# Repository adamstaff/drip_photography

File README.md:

# drip_photography
Board and code for a drip-photography timer

Based on 
https://petapixel.com/2016/06/04/build-diy-double-water-drip-system-high-speed-photos/

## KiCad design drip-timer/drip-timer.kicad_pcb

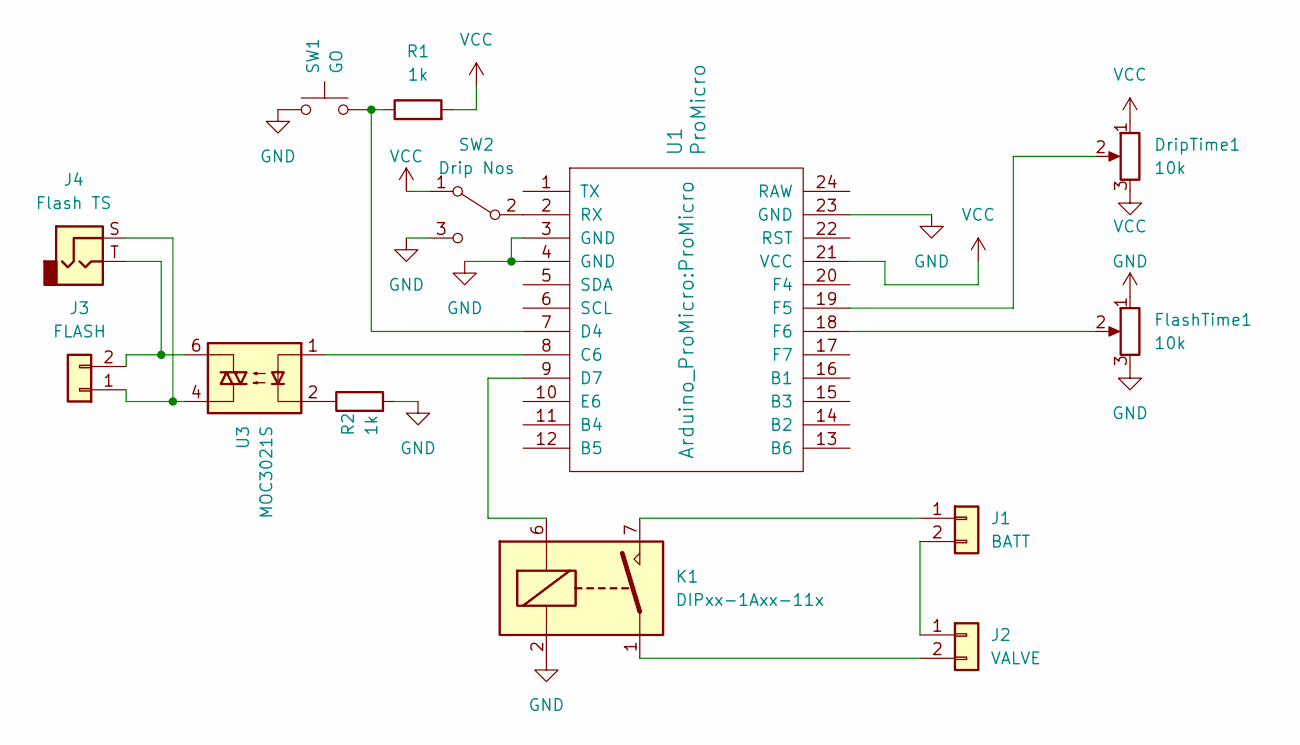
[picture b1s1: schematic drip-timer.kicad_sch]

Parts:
DripTime1: 10k; Potentiometer_Bourns_PTV09A-1_Single_Vertical
FlashTime1: 10k; Potentiometer_Bourns_PTV09A-1_Single_Vertical
J1: BATT; SolderWire-1sqmm_1x02_P5.4mm_D1.4mm_OD2.7mm_Relief
J2: VALVE; SolderWire-1sqmm_1x02_P5.4mm_D1.4mm_OD2.7mm_Relief
J3: FLASH; SolderWire-1sqmm_1x02_P5.4mm_D1.4mm_OD2.7mm_Relief
J4: Flash TS; Jack_3.5mm_CUI_SJ1-3523N_Horizontal
K1: DIPxx-1Axx-11x; Relay_StandexMeder_DIP_LowProfile
R1, R2: 1k; R_Axial_DIN0207_L6.3mm_D2.5mm_P7.62mm_Horizontal
SW1: GO; SW_PUSH_6mm
SW2: Drip Nos; SW_E-Switch_EG1271_SPDT
U1: ProMicro
U3: MOC3021S; SMDIP-6_W7.62mm

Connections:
GND: DripTime1.3, FlashTime1.3, K1.2, R2.2, SW1.1, SW2.3 (C), U1.3 (GND), U1.4 (GND), U1.23 (GND)
unnamed: J1.1, K1.7, K1.8
unnamed: J1.2, J2.1
unnamed: J2.2, K1.1, K1.14
unnamed: J3.1, J4.S, U3.4
unnamed: J3.2, J4.T, U3.6
unnamed: R2.1, U3.2
unnamed: SW2.2 (B), U1.2 (RX)
unnamed: U1.8 (C6), U3.1
unnamed: R1.1, SW1.2, U1.7 (D4)
unnamed: K1.6, U1.9 (D7)
unnamed: DripTime1.2, U1.19 (F5)
unnamed: FlashTime1.2, U1.18 (F6)
VCC: DripTime1.1, FlashTime1.1, R1.2, SW2.1 (A), U1.21 (VCC)

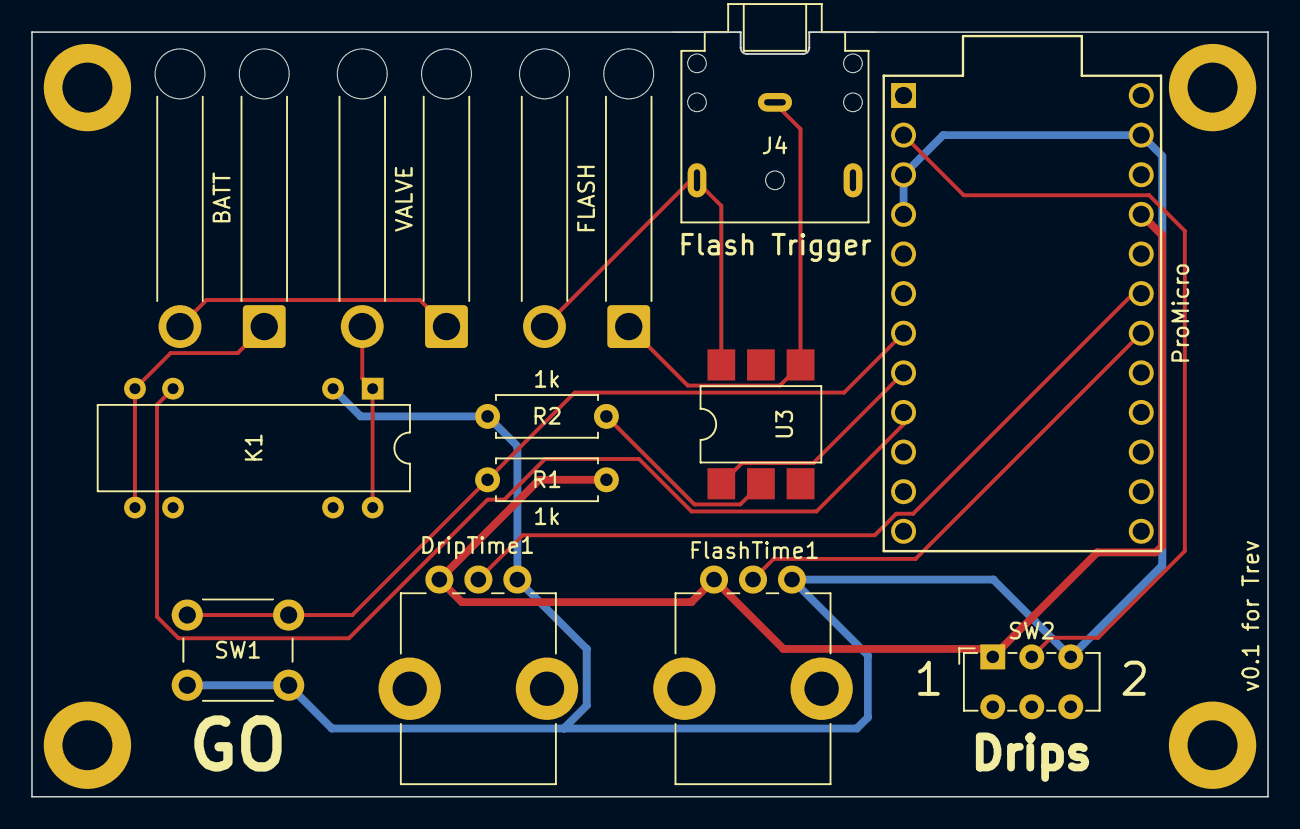
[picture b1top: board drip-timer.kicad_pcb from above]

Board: 2 copper layers, 79.2 x 49.0 mm, 13 parts (0 on the bottom side), 14 nets.

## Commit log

2023-10-08 Update README.md
    citation
2023-10-08 Update and rename arduino-code.txt to drip-photography.ino
    filename change
    set correct pins
2024-07-08 Add files via upload
    Many updates, including switches and pots for better control, layout changes etc
2024-07-15 completed work on v0.1 of pcb
